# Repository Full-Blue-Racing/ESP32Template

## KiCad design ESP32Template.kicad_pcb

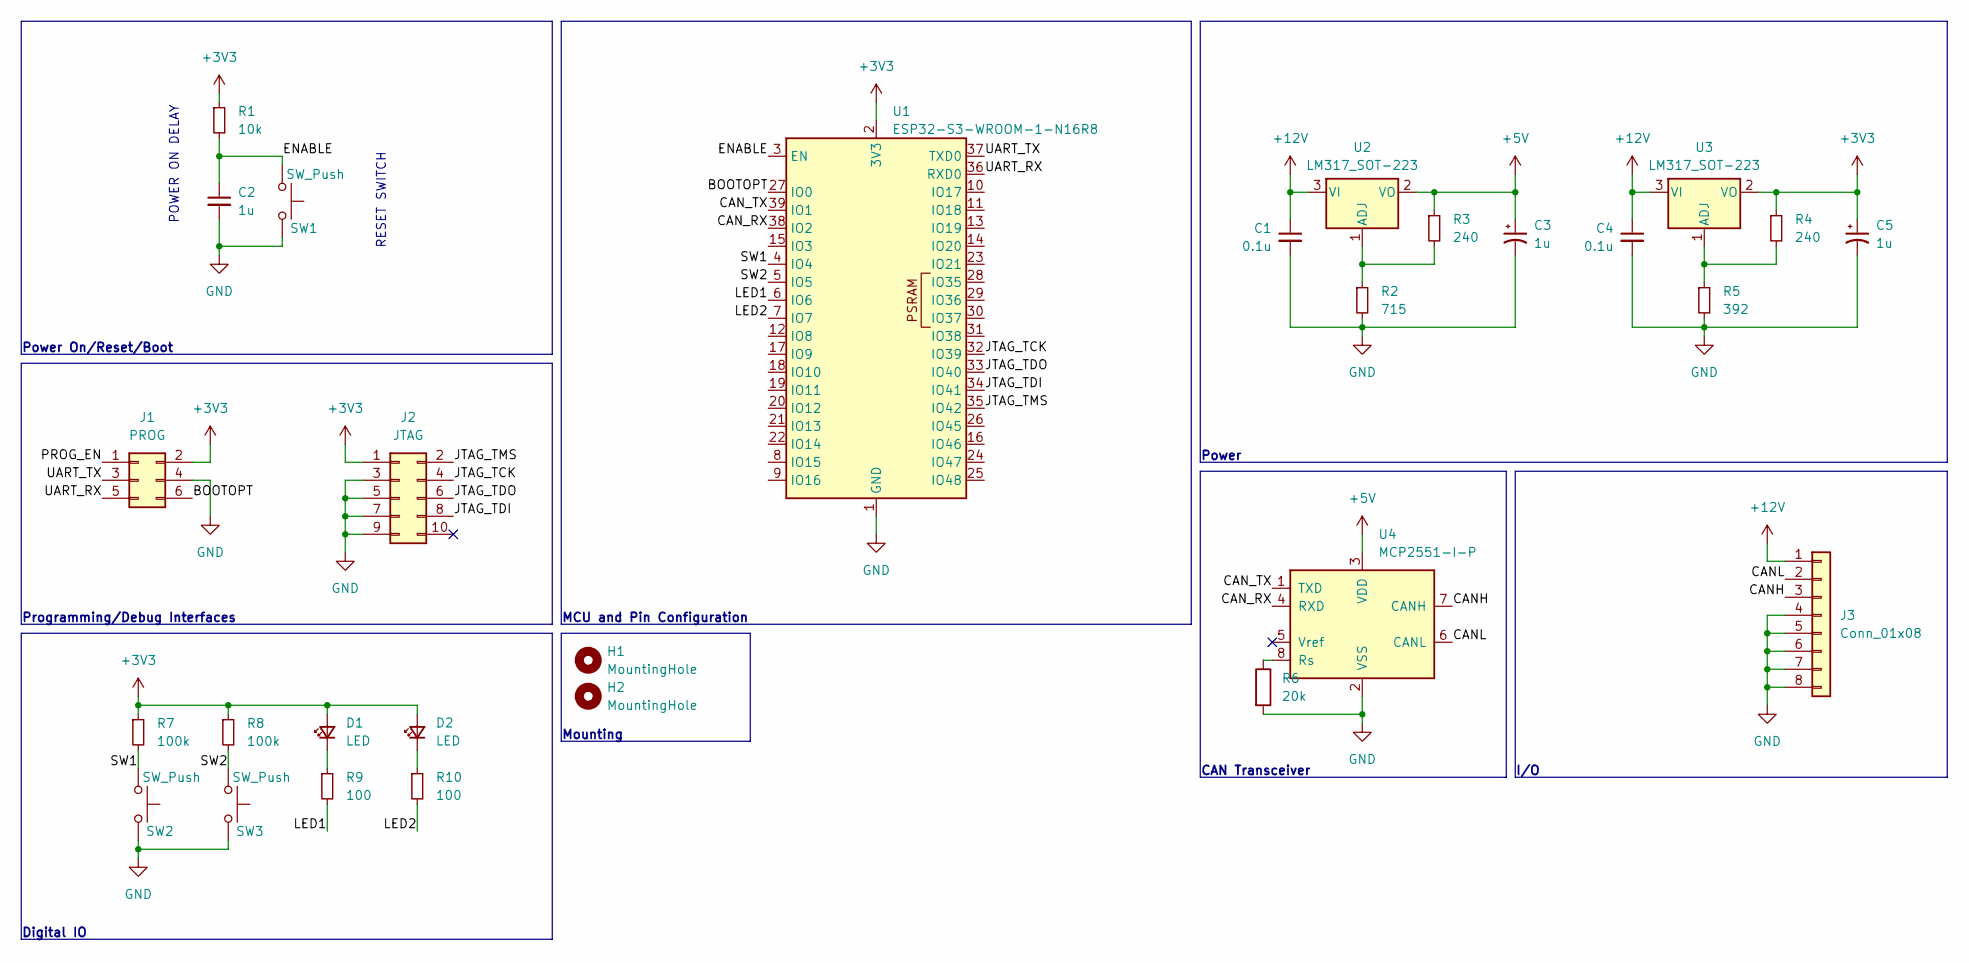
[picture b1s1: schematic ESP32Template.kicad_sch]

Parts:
C1, C4: 0.1u; C_Disc_D5.0mm_W2.5mm_P2.50mm
C2, C3, C5: 1u; C_Disc_D5.0mm_W2.5mm_P2.50mm
D1, D2: LED; LED_D5.0mm
H1, H2: MountingHole; MountingHole_3.2mm_M3
J1: PROG; PinHeader_2x03_P1.27mm_Vertical
J2: JTAG; PinHeader_2x05_P1.27mm_Vertical
J3: Conn_01x08; TE_776280-1
R1: 10k; R_Axial_DIN0207_L6.3mm_D2.5mm_P10.16mm_Horizontal
R2: 715; R_Axial_DIN0207_L6.3mm_D2.5mm_P10.16mm_Horizontal
R3, R4: 240; R_Axial_DIN0207_L6.3mm_D2.5mm_P10.16mm_Horizontal
R5: 392; R_Axial_DIN0207_L6.3mm_D2.5mm_P10.16mm_Horizontal
R6: 20k; R_Axial_DIN0207_L6.3mm_D2.5mm_P7.62mm_Horizontal
R7, R8: 100k; R_Axial_DIN0207_L6.3mm_D2.5mm_P7.62mm_Horizontal
R9, R10: 100; R_Axial_DIN0207_L6.3mm_D2.5mm_P7.62mm_Horizontal
SW1, SW2, SW3: SW_Push; SW_PUSH_1P1T_6x3.5mm_H4.3_APEM_MJTP1243
U1: ESP32-S3-WROOM-1-N16R8; ESP32-S3-WROOM-1
U2, U3: LM317_SOT-223; SOT-223-3_TabPin2
U4: MCP2551-I-P; DIP-8_W7.62mm

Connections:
+3V3: C5.1, D1.2 (A), D2.2 (A), J1.2, J2.1, R1.1, R4.1, R7.1, R8.1, U1.2 (3V3), U3.2 (VO)
+5V: C3.1, R3.1, U2.2 (VO), U4.3 (VDD)
+12V: C1.1, C4.1, J3.1, U2.3 (VI), U3.3 (VI)
/BOOTOPT: J1.6, U1.27 (IO0)
/CANH: J3.3, U4.7 (CANH)
/CANL: J3.2, U4.6 (CANL)
/CAN_RX: U1.38 (IO2), U4.4 (RXD)
/CAN_TX: U1.39 (IO1), U4.1 (TXD)
/ENABLE: C2.1, R1.2, SW1.1, U1.3 (EN)
/JTAG_TCK: J2.4, U1.32 (IO39)
/JTAG_TDI: J2.8, U1.34 (IO41)
/JTAG_TDO: J2.6, U1.33 (IO40)
/JTAG_TMS: J2.2, U1.35 (IO42)
/LED1: R9.2, U1.6 (IO6)
/LED2: R10.2, U1.7 (IO7)
/PROG_EN: J1.1
/SW1: R7.2, SW2.1, U1.4 (IO4)
/SW2: R8.2, SW3.1, U1.5 (IO5)
/UART_RX: J1.5, U1.36 (RXD0)
/UART_TX: J1.3, U1.37 (TXD0)
GND: C1.2, C2.2, C3.2, C4.2, C5.2, J1.4, J2.3, J2.5, J2.7, J2.9, J3.4, J3.5, J3.6, J3.7, J3.8, R2.2, R5.2, R6.2, SW1.2, SW2.2, SW3.2, U1.1 (GND), U1.40 (GND), U1.41 (GND), U4.2 (VSS)
unnamed: D1.1 (K), R9.1
unnamed: D2.1 (K), R10.1
unnamed: R2.1, R3.2, U2.1 (ADJ)
unnamed: R4.2, R5.1, U3.1 (ADJ)
unnamed: R6.1, U4.8 (Rs)

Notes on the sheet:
RESET SWITCH
Power On/Reset/Boot
Mounting
MCU and Pin Configuration
Power
POWER ON DELAY
CAN Transceiver
Digital IO
Programming/Debug Interfaces
I/O

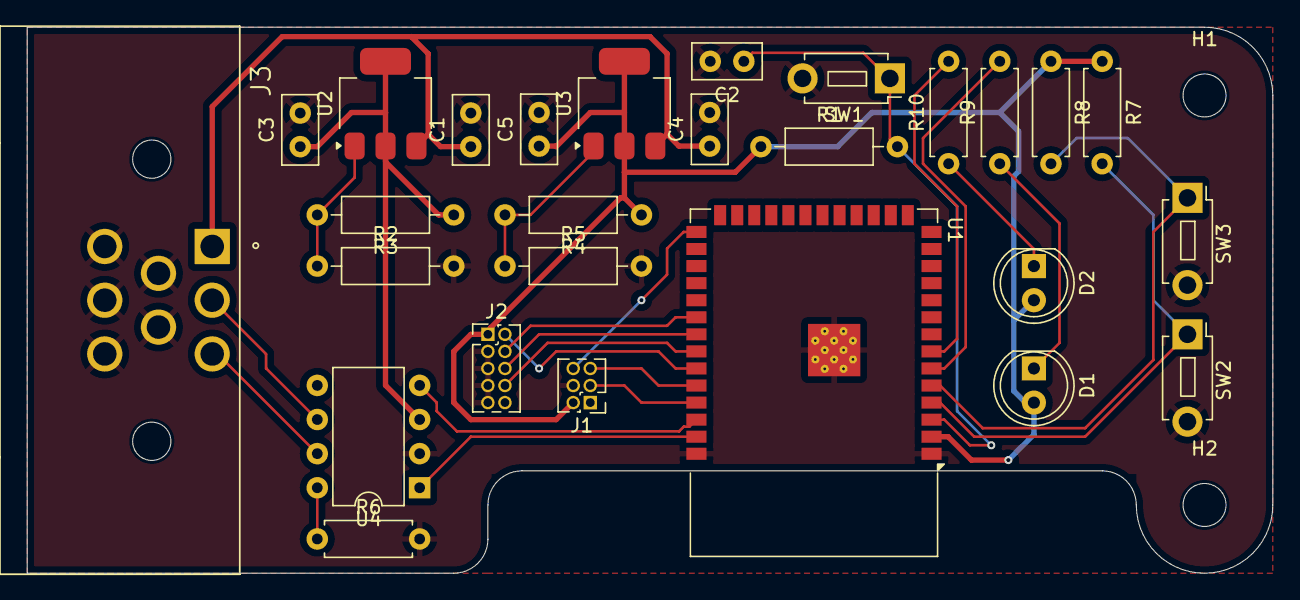
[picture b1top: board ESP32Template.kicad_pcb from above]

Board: 2 copper layers, 92.7 x 40.6 mm, 29 parts (0 on the bottom side), 25 nets.

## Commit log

2024-11-13 Initial version.
2024-11-14 Example PCB v1
2024-11-14 Footprint Assignment
